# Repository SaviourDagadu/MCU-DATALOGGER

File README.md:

# MCU-DATALOGGER
Mcu data logger purposefully logs sensor datas integrated to the system for efficient data capturing and Monitoring of data for future use.

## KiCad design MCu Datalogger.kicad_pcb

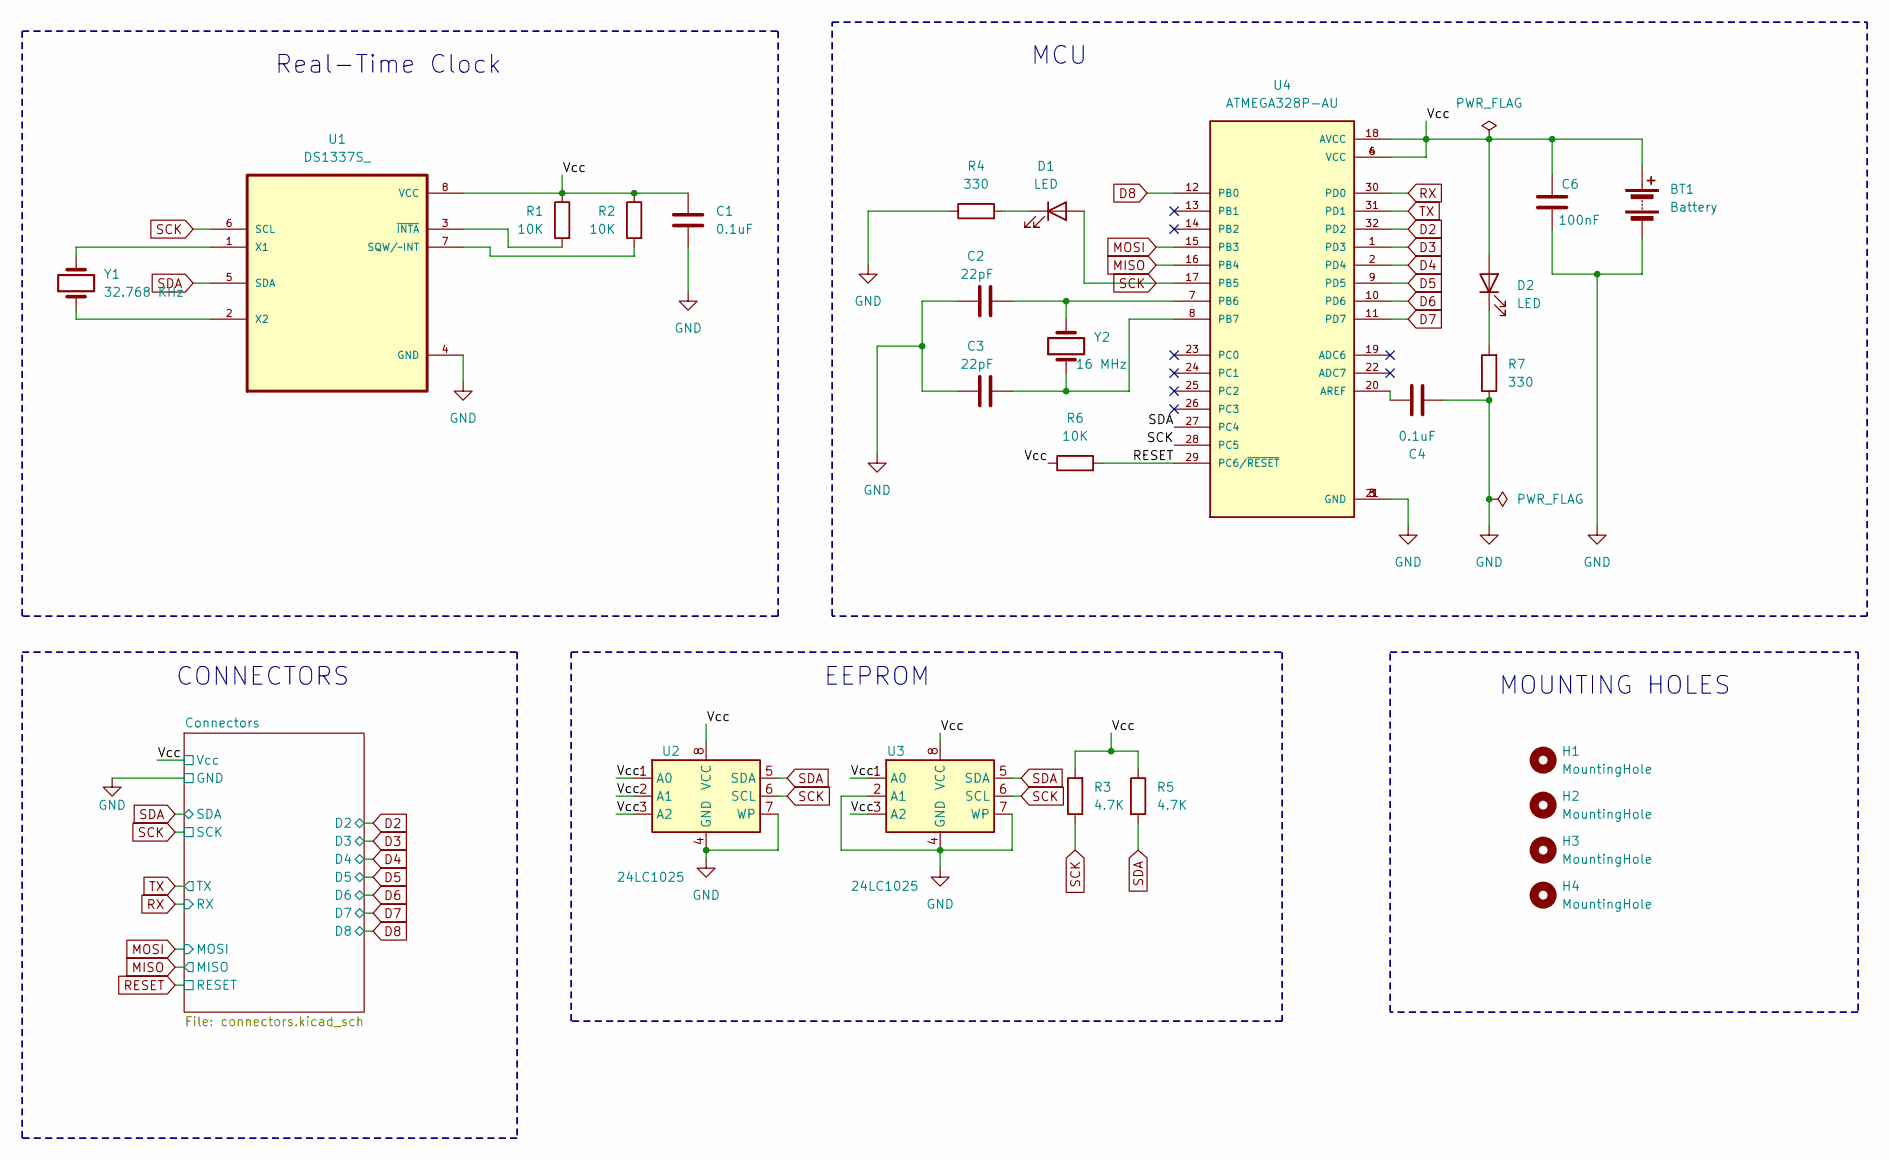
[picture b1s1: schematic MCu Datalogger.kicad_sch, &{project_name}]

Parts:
BT1: Battery; PinHeader_1x02_P2.54mm_Vertical
C1, C4: 0.1uF; C_0805_2012Metric
C2, C3: 22pF; C_0805_2012Metric
C6: 100nF; C_0805_2012Metric
D1, D2: LED; LED_0805_2012Metric
H1, H2, H3, H4: MountingHole; MountingHole_2.1mm
R1, R2, R6: 10K; R_0805_2012Metric
R3, R5: 4.7K; R_0805_2012Metric
R4, R7: 330; R_0805_2012Metric
U1: DS1337S_; SOIC127P600X175-8N
U2, U3: 24LC1025; SOIC-8_3.9x4.9mm_P1.27mm
U4: ATMEGA328P-AU; QFP80P900X900X120-32N; PARTREV 8271A
Y1: 32.768 KHz; Crystal_SMD_5032-2Pin_5.0x3.2mm_HandSoldering
Y2: 16 MHz; Crystal_SMD_5032-2Pin_5.0x3.2mm_HandSoldering

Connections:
/Vcc: BT1.1 (+), C1.1, C6.2, D2.2 (A), R1.1, R2.1, R3.2, R5.1, R6.1, U1.8 (VCC), U2.1 (A0), U2.2 (A1), U2.3 (A2), U2.8 (VCC), U3.1 (A0), U3.3 (A2), U3.8 (VCC), U4.4 (VCC), U4.6 (VCC), U4.18 (AVCC); also elsewhere on the board
D2: U4.32 (PD2); also elsewhere on the board
D3: U4.1 (PD3); also elsewhere on the board
D4: U4.2 (PD4); also elsewhere on the board
D5: U4.9 (PD5); also elsewhere on the board
D6: U4.10 (PD6); also elsewhere on the board
D7: U4.11 (PD7); also elsewhere on the board
D8: U4.12 (PB0); also elsewhere on the board
GND: BT1.2 (-), C1.2, C2.1, C3.1, C4.2, C6.1, R4.1, R7.1, U1.4 (GND), U2.4 (GND), U2.7 (WP), U3.2 (A1), U3.4 (GND), U3.7 (WP), U4.3 (GND), U4.5 (GND), U4.21 (GND); also elsewhere on the board
MISO: U4.16 (PB4); also elsewhere on the board
MOSI: U4.15 (PB3); also elsewhere on the board
unnamed: D1.1 (K), R4.2
unnamed: D2.1 (K), R7.2
unnamed: R2.2, U1.7 (SQW/~INT)
unnamed: U1.1 (X1), Y1.2
unnamed: U1.2 (X2), Y1.1
unnamed: R1.2, U1.3 (~INTA)
unnamed: C4.1, U4.20 (AREF)
unnamed: C2.2, U4.7 (PB6), Y2.2
unnamed: C3.2, U4.8 (PB7), Y2.1
RESET: R6.2, U4.29 (PC6/~RESET); also elsewhere on the board
RX: U4.30 (PD0); also elsewhere on the board
SCK: D1.2 (A), R3.1, U1.6 (SCL), U2.6 (SCL), U3.6 (SCL), U4.17 (PB5), U4.28 (PC5); also elsewhere on the board
SDA: R5.2, U1.5 (SDA), U2.5 (SDA), U3.5 (SDA), U4.27 (PC4); also elsewhere on the board
TX: U4.31 (PD1); also elsewhere on the board

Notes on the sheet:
MCU
MOUNTING HOLES
EEPROM
Real-Time Clock
CONNECTORS

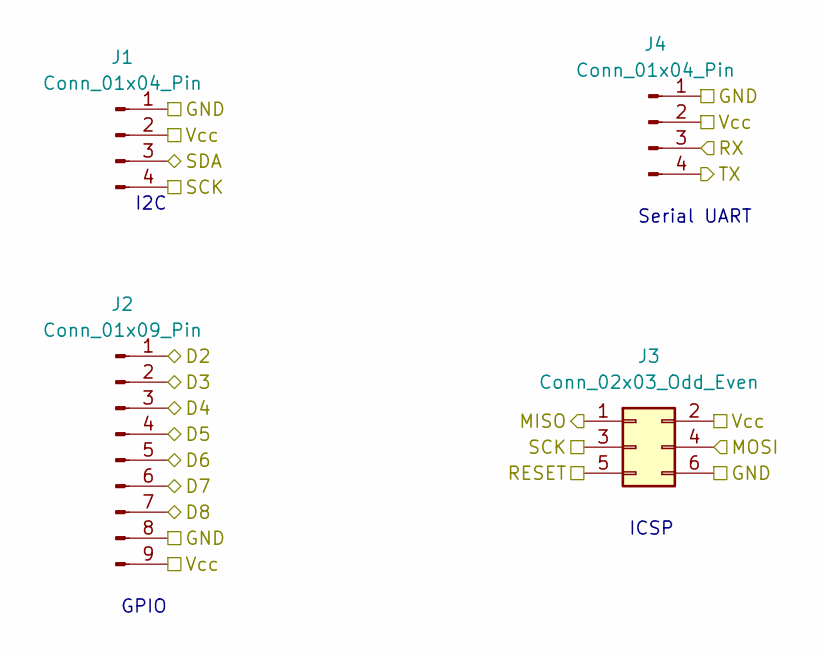
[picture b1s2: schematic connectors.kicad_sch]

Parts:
J1, J4: Conn_01x04_Pin; PinHeader_1x04_P2.54mm_Vertical
J2: Conn_01x09_Pin; PinHeader_1x09_P2.54mm_Vertical
J3: Conn_02x03_Odd_Even; PinHeader_2x03_P2.54mm_Vertical

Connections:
/Vcc: J1.2, J2.9, J3.2, J4.2; also elsewhere on the board
D2: J2.1; also elsewhere on the board
D3: J2.2; also elsewhere on the board
D4: J2.3; also elsewhere on the board
D5: J2.4; also elsewhere on the board
D6: J2.5; also elsewhere on the board
D7: J2.6; also elsewhere on the board
D8: J2.7; also elsewhere on the board
GND: J1.1, J2.8, J3.6, J4.1; also elsewhere on the board
MISO: J3.1; also elsewhere on the board
MOSI: J3.4; also elsewhere on the board
RESET: J3.5; also elsewhere on the board
RX: J4.3; also elsewhere on the board
SCK: J1.4, J3.3; also elsewhere on the board
SDA: J1.3; also elsewhere on the board
TX: J4.4; also elsewhere on the board

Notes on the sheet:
I2C
GPIO
Serial UART
ICSP

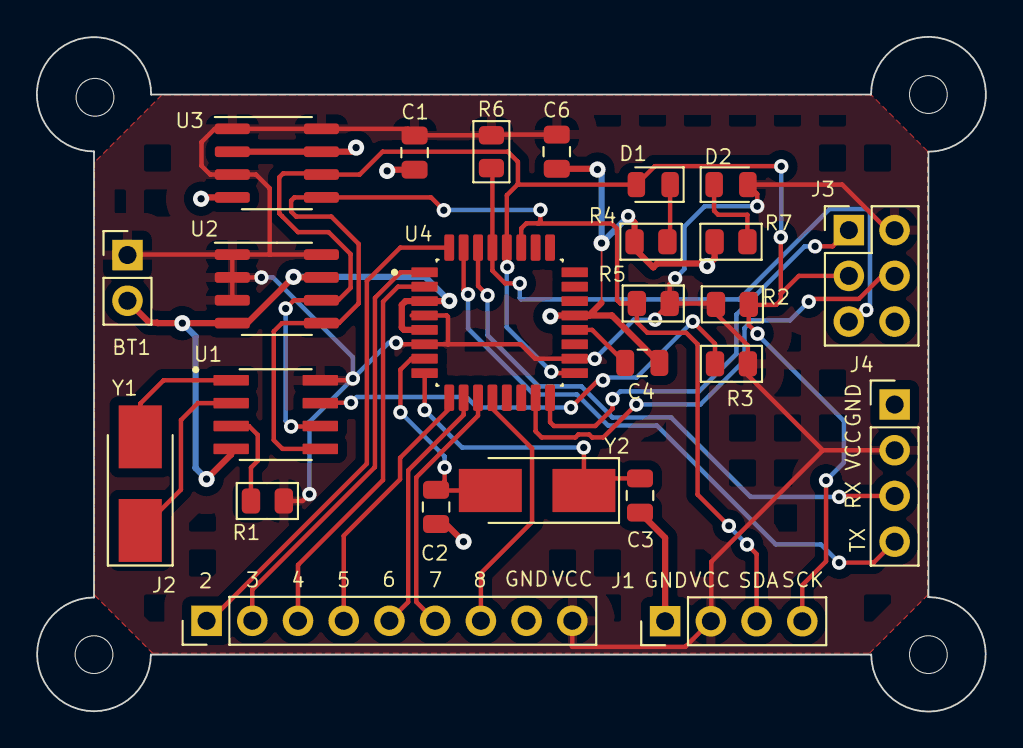
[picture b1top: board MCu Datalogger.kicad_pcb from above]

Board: 2 copper layers, 52.7 x 37.5 mm, 29 parts (0 on the bottom side), 25 nets.

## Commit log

2024-09-17 updating of design files to the diretory
